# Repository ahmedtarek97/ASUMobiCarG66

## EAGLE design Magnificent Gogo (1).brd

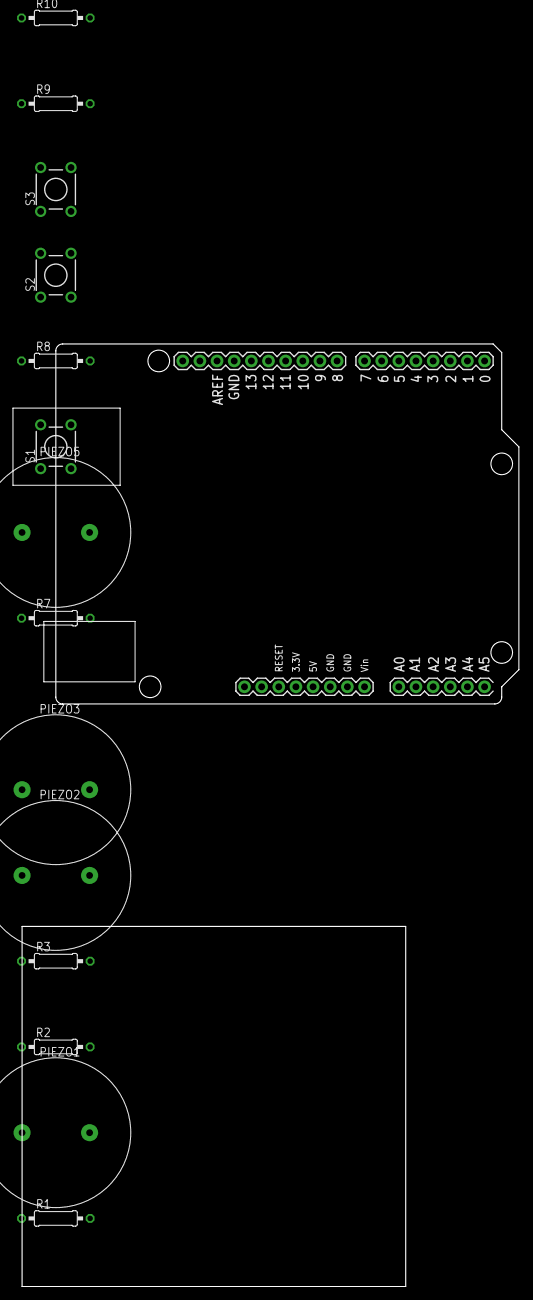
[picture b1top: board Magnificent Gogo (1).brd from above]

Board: 2 copper layers, 15 parts (0 on the bottom side), 13 nets, no tracks yet.

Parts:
PIEZO1, PIEZO2, PIEZO3, PIEZO5: PIEZO-22MM
R1, R2, R3, R7: 100‎Ω; 0207/10
R8, R9, R10: 10k‎Ω; 0207/10
S1, S2, S3: TL1105
U1: ARDUINO_UNO

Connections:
unnamed: PIEZO3.P$1, R3.2
unnamed: PIEZO2.P$1, R2.2
unnamed: PIEZO1.P$1, R1.2
unnamed: R7.2, R8.2, R9.2, R10.2, U1.GND..
unnamed: PIEZO5.P$2, U1.8
unnamed: PIEZO5.P$1, R7.1
unnamed: S1.2, S2.2, S3.2, U1.5V
unnamed: R8.1, S1.1
unnamed: S1.3, U1.A0
unnamed: R9.1, S2.1
unnamed: S2.3, U1.A1
unnamed: R10.1, S3.1
unnamed: S3.3, U1.A2

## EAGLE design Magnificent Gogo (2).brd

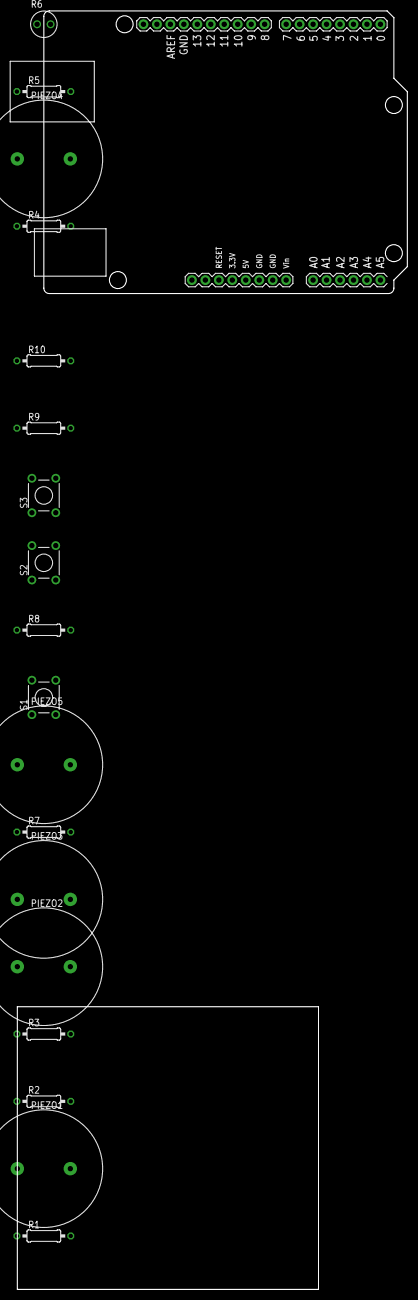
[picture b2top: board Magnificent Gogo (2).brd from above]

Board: 2 copper layers, 73.6 x 241.2 mm, 19 parts (0 on the bottom side), 9 nets, no tracks yet.

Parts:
PIEZO1, PIEZO2, PIEZO3, PIEZO4, PIEZO5: PIEZO-22MM
R1, R2, R3, R4, R7: 100‎Ω; 0207/10
R5: 4.7k‎Ω; 0207/10
R6: PHOTORESISTOR-2.54
R8, R9, R10: 10k‎Ω; 0207/10
S1, S2, S3: TL1105
U1: ARDUINO_UNO

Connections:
unnamed: PIEZO3.P$1, R3.2
unnamed: PIEZO2.P$1, R2.2
unnamed: PIEZO1.P$1, R1.2
unnamed: R4.2, U1.9
unnamed: PIEZO4.P$1, R4.1
unnamed: PIEZO4.P$2, U1.GND
unnamed: R5.2, U1.GND.
unnamed: R5.1, R6.P$1, U1.A0
unnamed: R6.P$2, U1.5V

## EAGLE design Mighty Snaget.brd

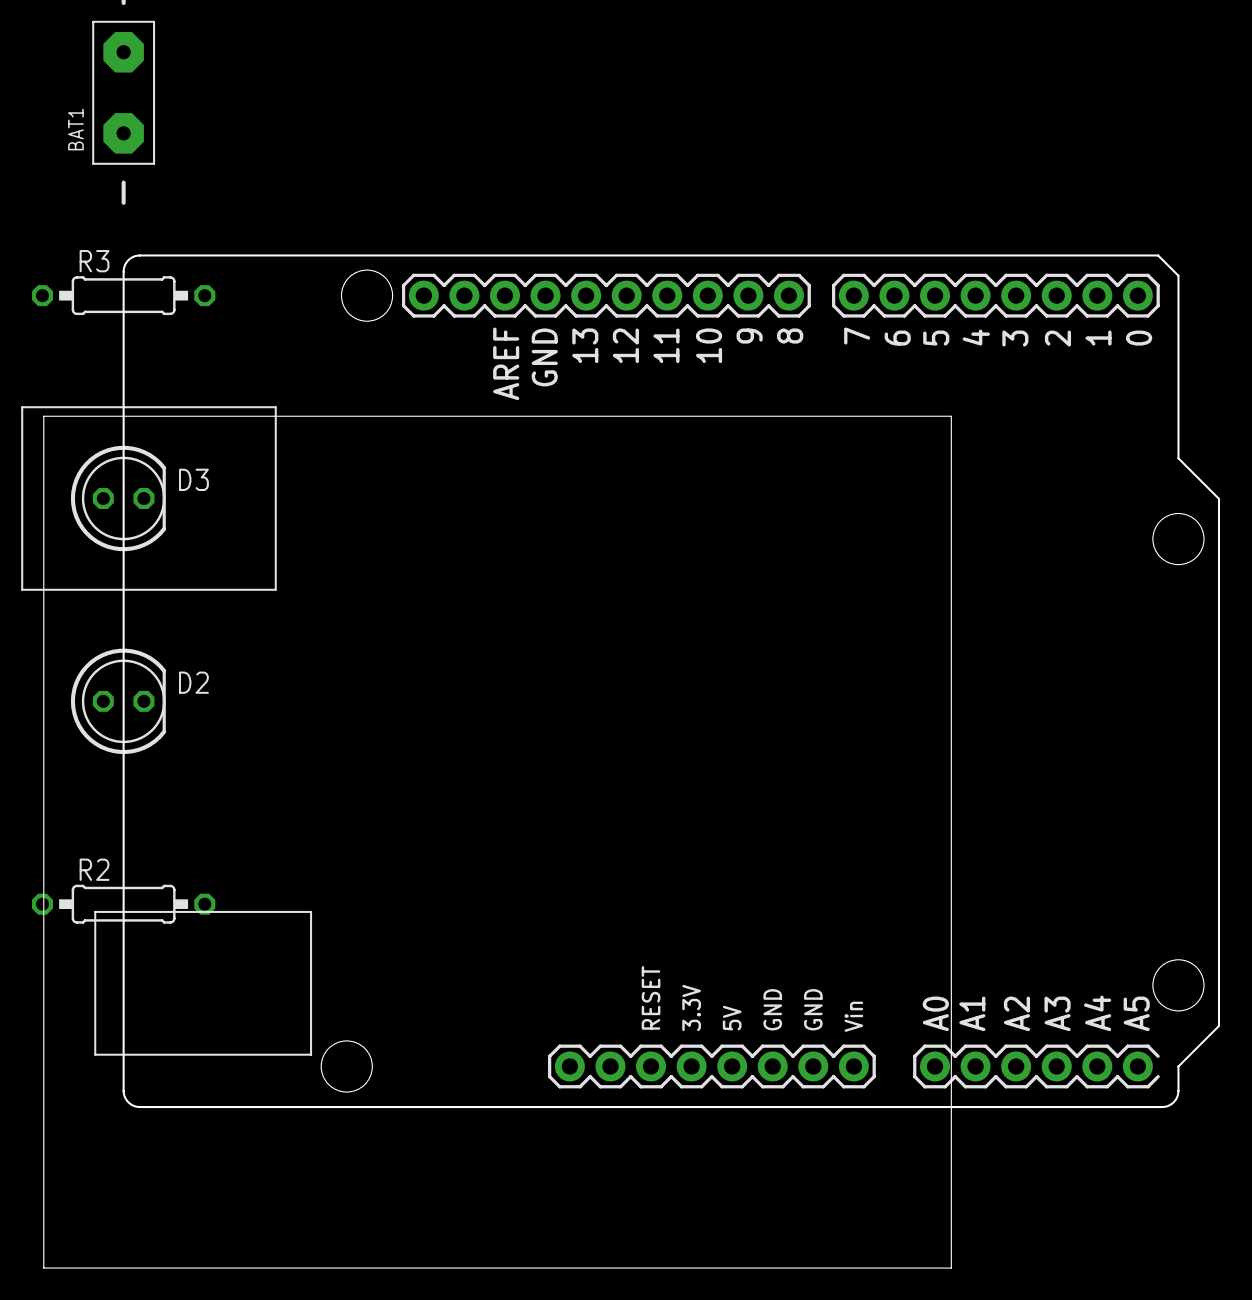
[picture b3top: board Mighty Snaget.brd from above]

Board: 2 copper layers, 73.6 x 63.4 mm, 6 parts (0 on the bottom side), 7 nets, no tracks yet.

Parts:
BAT1: DC-POWER
D2, D3: LED5MM
R2, R3: 200‎Ω; 0207/10
U3: ARDUINO_UNO

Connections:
unnamed: D2.A, R2.2
unnamed: D2.K, D3.K, U3.GND
unnamed: R2.1, U3.2
unnamed: D3.A, R3.2
unnamed: R3.1, U3.3
unnamed: BAT1.-, U3.GND.
unnamed: BAT1.+, U3.VIN

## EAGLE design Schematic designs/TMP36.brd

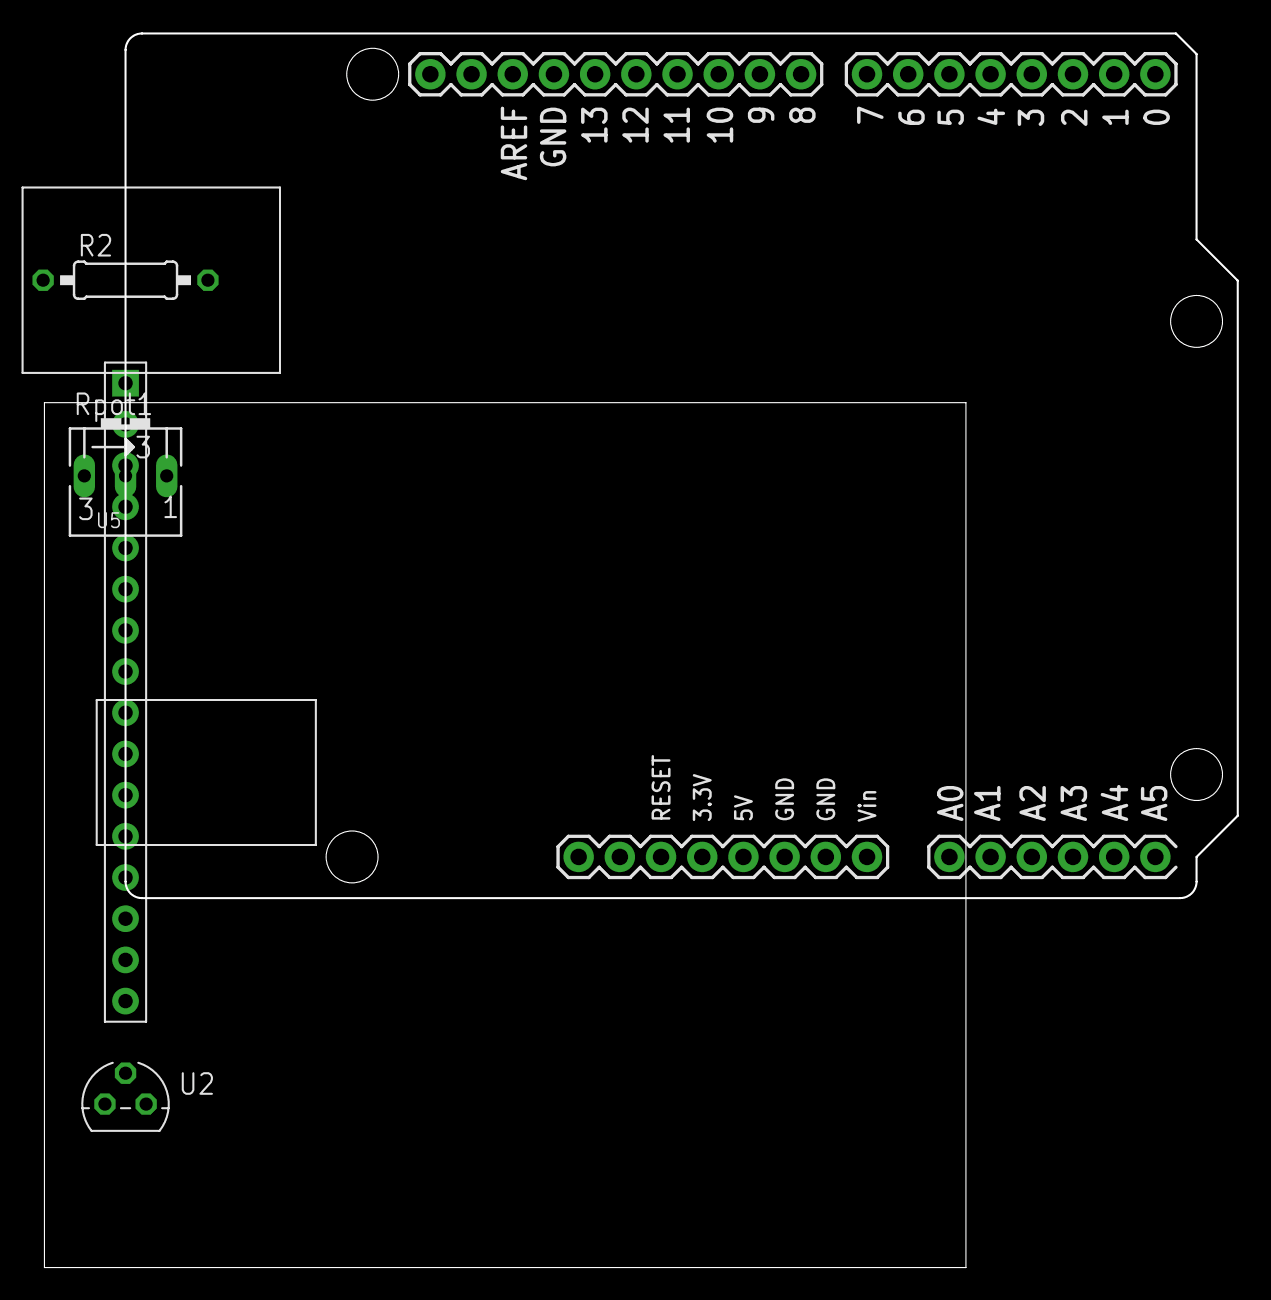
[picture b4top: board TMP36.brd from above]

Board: 2 copper layers, 73.6 x 76.1 mm, 5 parts (0 on the bottom side), 11 nets, no tracks yet.

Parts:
R2: 220‎Ω; 0207/10
Rpot1: 250k‎Ω; B25V
U1: ARDUINO_UNO
U2: TO92
U5: 1X16P-2.54-2.54-11.6-3.0-BLACK-MALE

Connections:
unnamed: Rpot1.E, U1.GND.., U2.1, U5.1, U5.5, U5.16
unnamed: U1.12, U5.4
unnamed: U1.11, U5.6
unnamed: U1.5, U5.11
unnamed: U1.4, U5.12
unnamed: U1.3, U5.13
unnamed: U1.2, U5.14
unnamed: Rpot1.S, U5.3
unnamed: R2.2, U5.15
unnamed: R2.1, Rpot1.A, U1.5V, U2.3, U5.2
unnamed: U1.A0, U2.2

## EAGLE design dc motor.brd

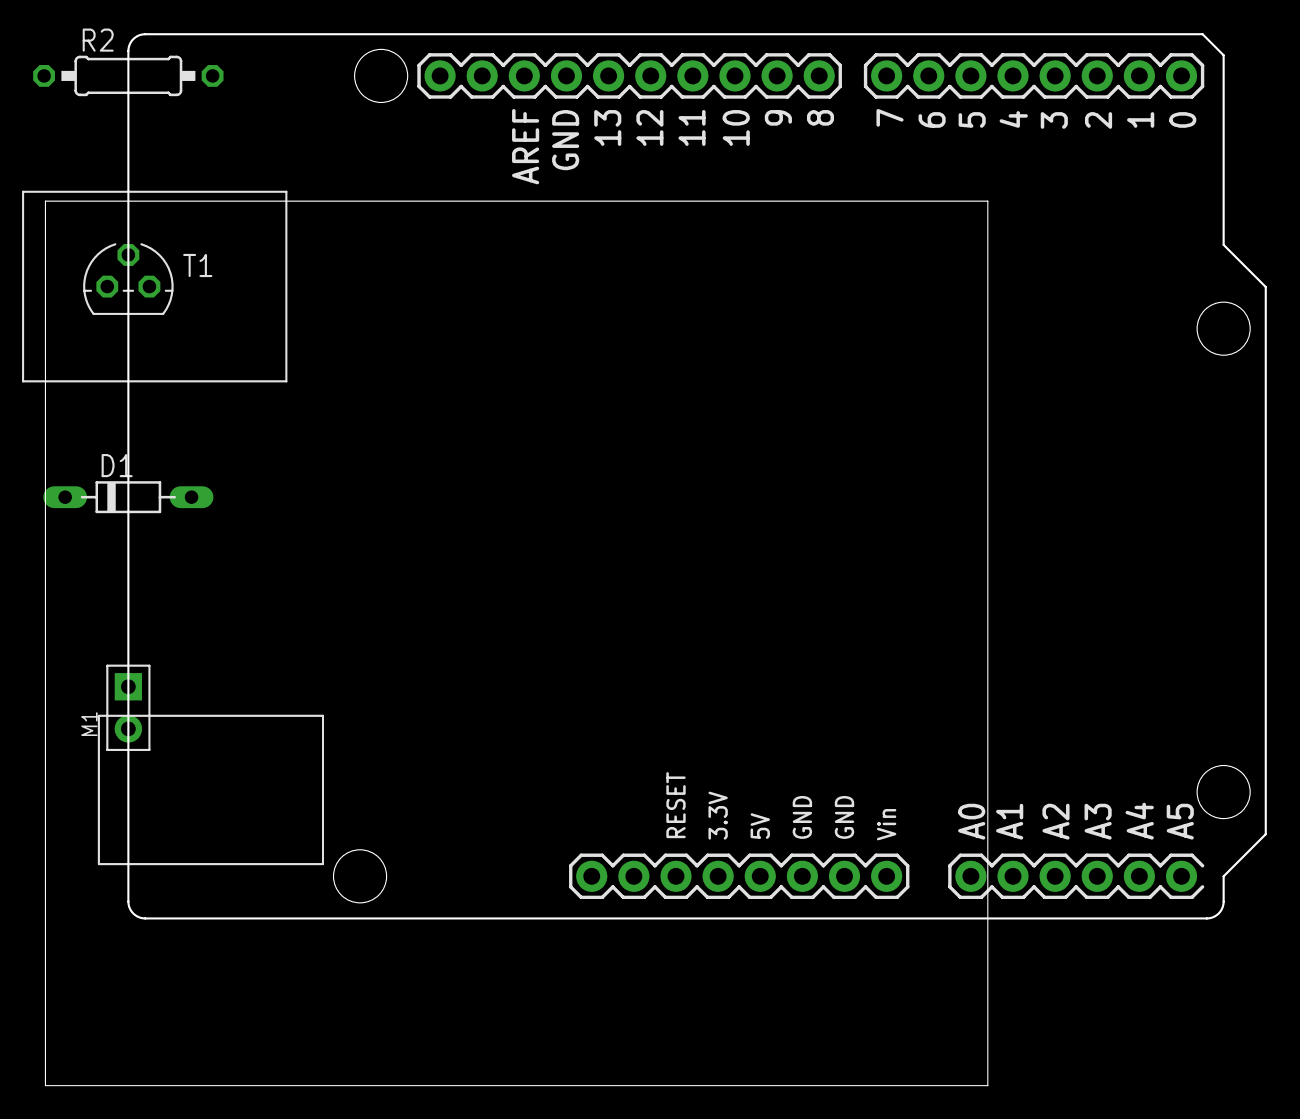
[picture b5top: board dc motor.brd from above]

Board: 2 copper layers, 73.6 x 63.4 mm, 5 parts (0 on the bottom side), 5 nets, no tracks yet.

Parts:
D1: D-7.5
M1: 2P-2.54-65/35MIL
R2: 1k‎Ω; 0207/10
T1: TO92
U1: ARDUINO_UNO

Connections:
unnamed: D1.C, M1.1, U1.5V
unnamed: D1.A, M1.2, T1.1
unnamed: R2.1, T1.2
unnamed: R2.2, U1.A0
unnamed: T1.3, U1.GND.

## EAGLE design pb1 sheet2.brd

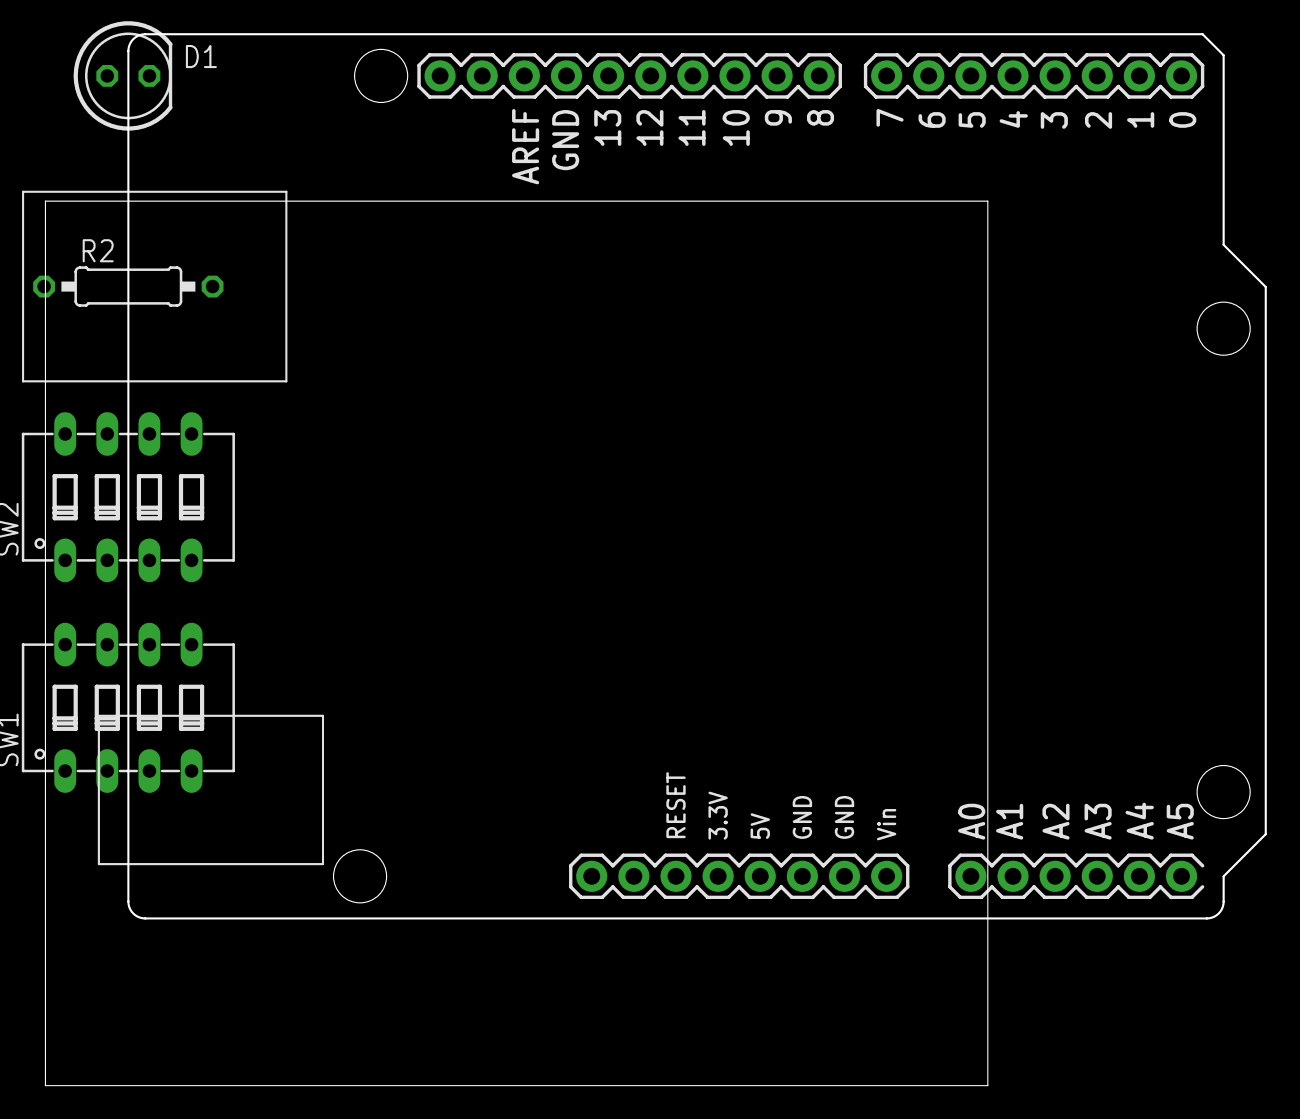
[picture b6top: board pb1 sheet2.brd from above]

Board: 2 copper layers, 73.6 x 63.4 mm, 5 parts (0 on the bottom side), 12 nets, no tracks yet.

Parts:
D1: LED5MM
R2: 220‎Ω; 0207/10
SW1, SW2: DIP04YL
U1: ARDUINO_UNO

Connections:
unnamed: SW1.1, SW1.2, SW1.3, SW1.4, SW2.1, SW2.2, SW2.3, SW2.4, U1.5V
unnamed: SW1.8, U1.0
unnamed: SW1.7, U1.1
unnamed: SW1.6, U1.2
unnamed: SW1.5, U1.3
unnamed: SW2.8, U1.4
unnamed: SW2.7, U1.5
unnamed: SW2.6, U1.6
unnamed: SW2.5, U1.7
unnamed: D1.A, R2.1
unnamed: D1.K, U1.GND.
unnamed: R2.2, U1.8

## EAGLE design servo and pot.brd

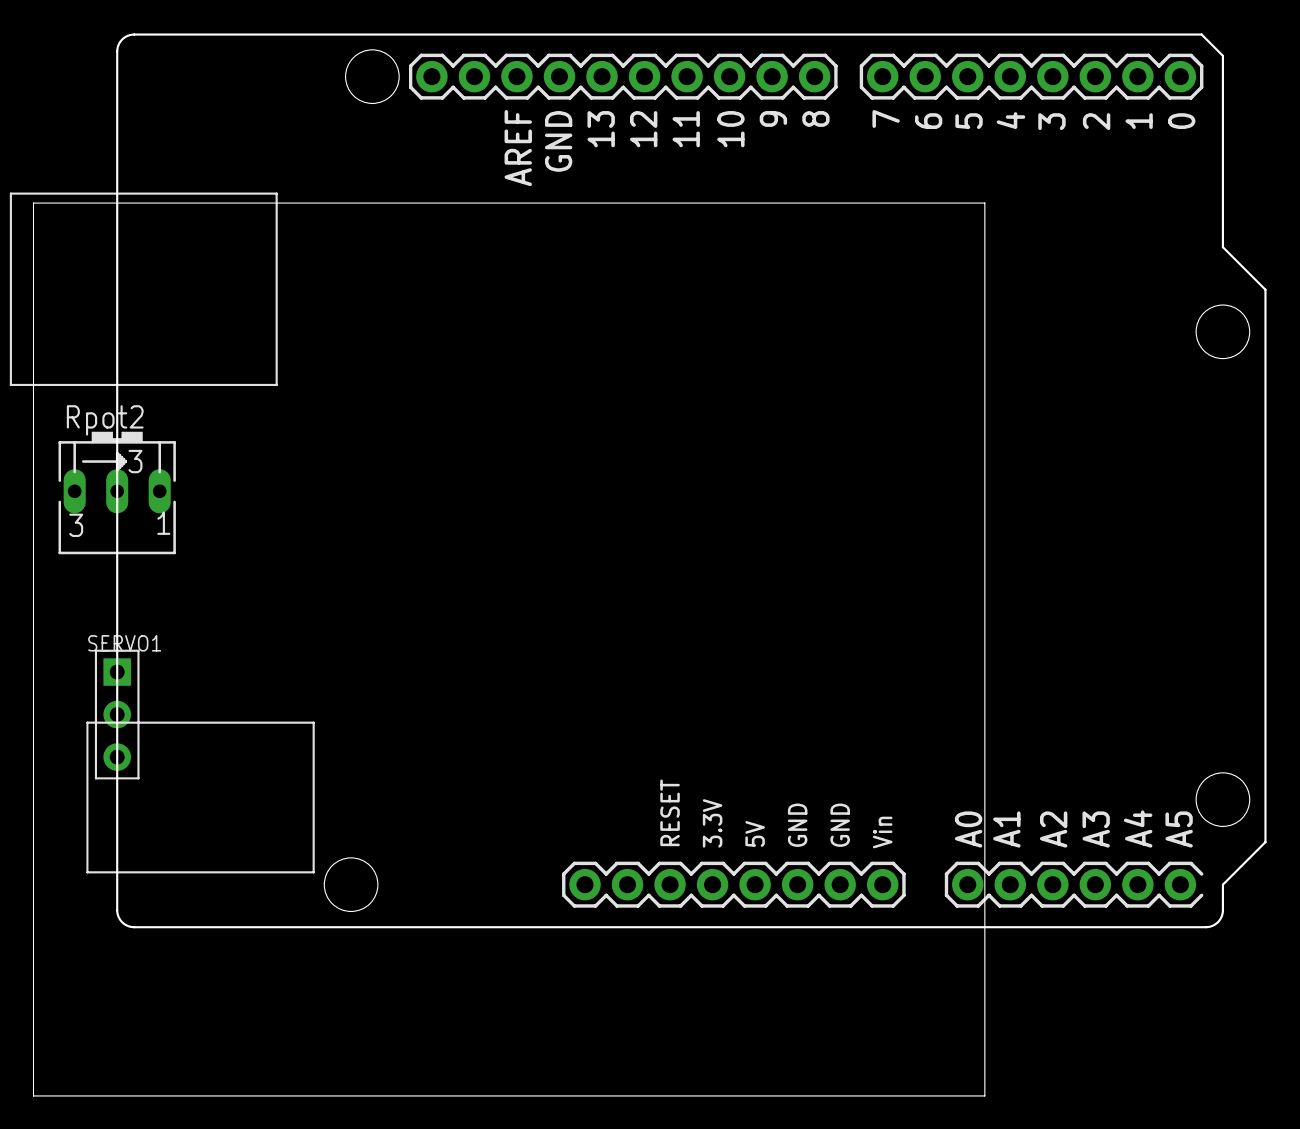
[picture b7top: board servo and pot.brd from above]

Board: 2 copper layers, 73.6 x 63.4 mm, 3 parts (0 on the bottom side), 5 nets, no tracks yet.

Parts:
Rpot2: 250k‎Ω; B25V
SERVO1: 1X3P-2.54-2.54-11.6-3.0-BLACK-MALE
U1: ARDUINO_UNO

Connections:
unnamed: SERVO1.1, U1.GND.
unnamed: Rpot2.A, SERVO1.2, U1.5V
unnamed: SERVO1.3, U1.7
unnamed: Rpot2.E, U1.GND..
unnamed: Rpot2.S, U1.A0
